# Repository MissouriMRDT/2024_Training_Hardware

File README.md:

# 2024_Training_Hardware
Useless Schematics and PCB Layouts for Training Purposes

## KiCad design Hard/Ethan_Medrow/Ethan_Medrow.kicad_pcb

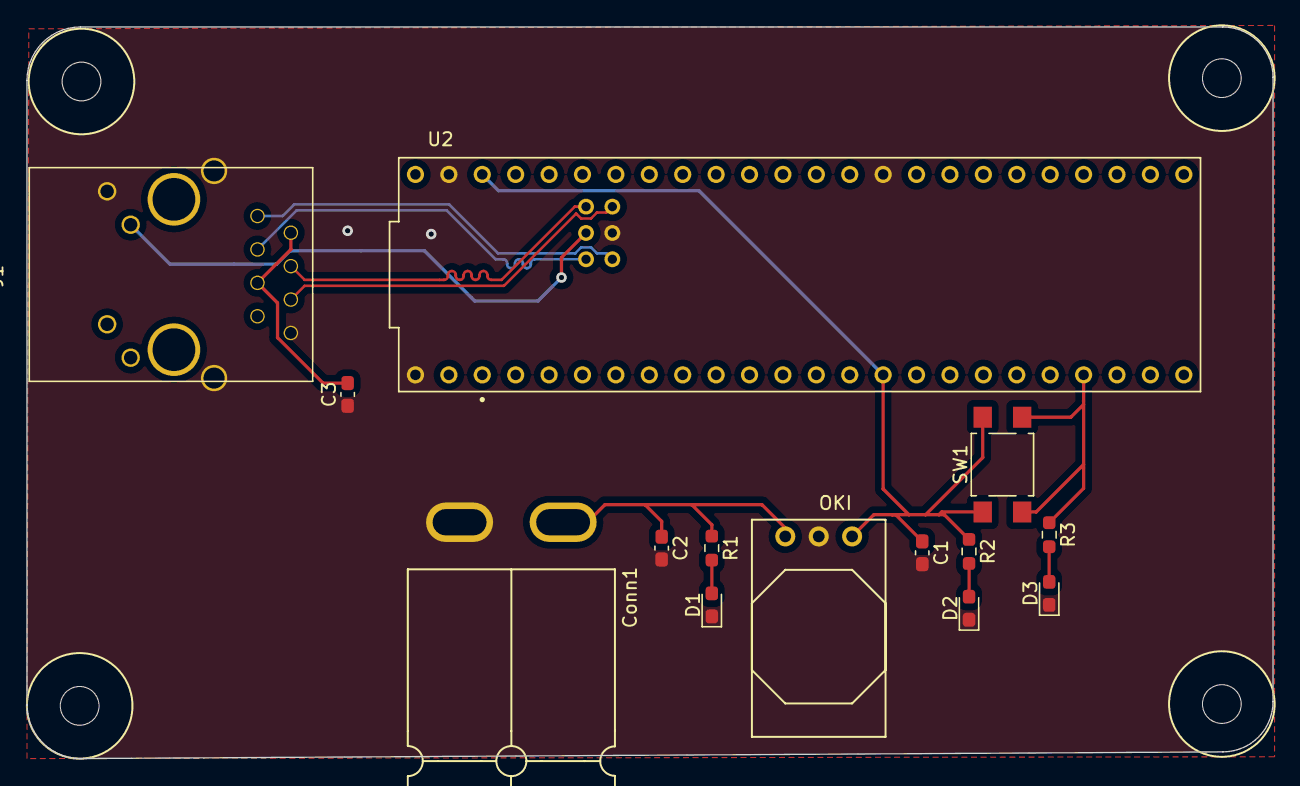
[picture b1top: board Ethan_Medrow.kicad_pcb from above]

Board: 2 copper layers, 94.7 x 55.6 mm, 14 parts (0 on the bottom side), 13 nets.

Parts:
C1, C2: 10uF; C_0603_1608Metric_Pad1.08x0.95mm_HandSolder
C3: 0.1uF; C_0603_1608Metric_Pad1.08x0.95mm_HandSolder
Conn1: AndersonPP; Square_Anderson_2_H_Side_By_Side_PV
D1, D2, D3: Green; LED_0603_1608Metric_Pad1.05x0.95mm_HandSolder
J1: RJ45_LED_Shielded; RJ45_Teensy
R1: 3k; R_0603_1608Metric_Pad0.98x0.95mm_HandSolder
R2, R3: 120; R_0603_1608Metric_Pad0.98x0.95mm_HandSolder
SW1: SW_Push; SW_SPST_TL3305A
U1: OKI; OKI_Horizontal
U2: Teensy4.1_DEV-16771; Teensy_4_1_Ethernet

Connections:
+3V3: C1.1, R2.1, SW1.1, U1.3 (Vo), U2.3.3V_1 (3.3V), U2.3.3V_2 (3.3V)
/R+: J1.4, U2.R+
/R-: J1.6, U2.R-
/T+: J1.1, U2.T+
/T-: J1.3, U2.T-
GND: C1.2, C2.2, C3.1, Conn1.1 (GND), D1.1 (K), D2.1 (K), D3.1 (K), J1.8, J1.9, J1.SH, U1.2 (GND), U2.GND1 (GND), U2.GND2 (GND), U2.GND3 (GND), U2.GND5 (GND)
unnamed: C3.2, J1.2, J1.5
unnamed: D1.2 (A), R1.2
unnamed: D2.2 (A), R2.2
unnamed: D3.2 (A), R3.2
unnamed: J1.10, U2.LED
PV: C2.1, Conn1.4 (PV+), R1.1, U1.1 (Vi)
Test_Button: R3.1, SW1.2, U2.29 (TX7)

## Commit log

2023-09-01 Finished Training Schematic
2023-09-02 Training Completed
2023-09-02 Training Completed
    Added a teensy, LED, button, Oki, and power schematic
2023-09-02 Training Files
2023-09-02 Training Complete
2023-09-02 Made some things
    Made some things but idk what they do
2023-09-02 Did schematic training
2023-09-09 training complete (maybe)
2023-10-01 uh yeah it's done
2023-10-01 Finished Layout Training
2023-10-01 layout training 10/1/23
2023-10-01 Layout Training Finished
2023-10-01 Layout Training completed
    yup
2023-10-01 Added image to layout training
    :)
2023-10-03 Layout Training complete
    Learned dat junks
2023-10-03 Layout Training Complete
    :)
2023-10-03 Layout Training
2023-10-16 completed rev1 rough draft
2023-10-17 layout Training complete
2023-10-19 Layout Done
